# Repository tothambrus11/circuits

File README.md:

# My PCBs
I collect my PCB designs here.

## Categories
- [Audio circuits](audio-circuits/)

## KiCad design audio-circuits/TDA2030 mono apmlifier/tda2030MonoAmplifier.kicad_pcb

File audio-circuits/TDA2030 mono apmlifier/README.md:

# 1x18w mono amplifier

## PCB layout:

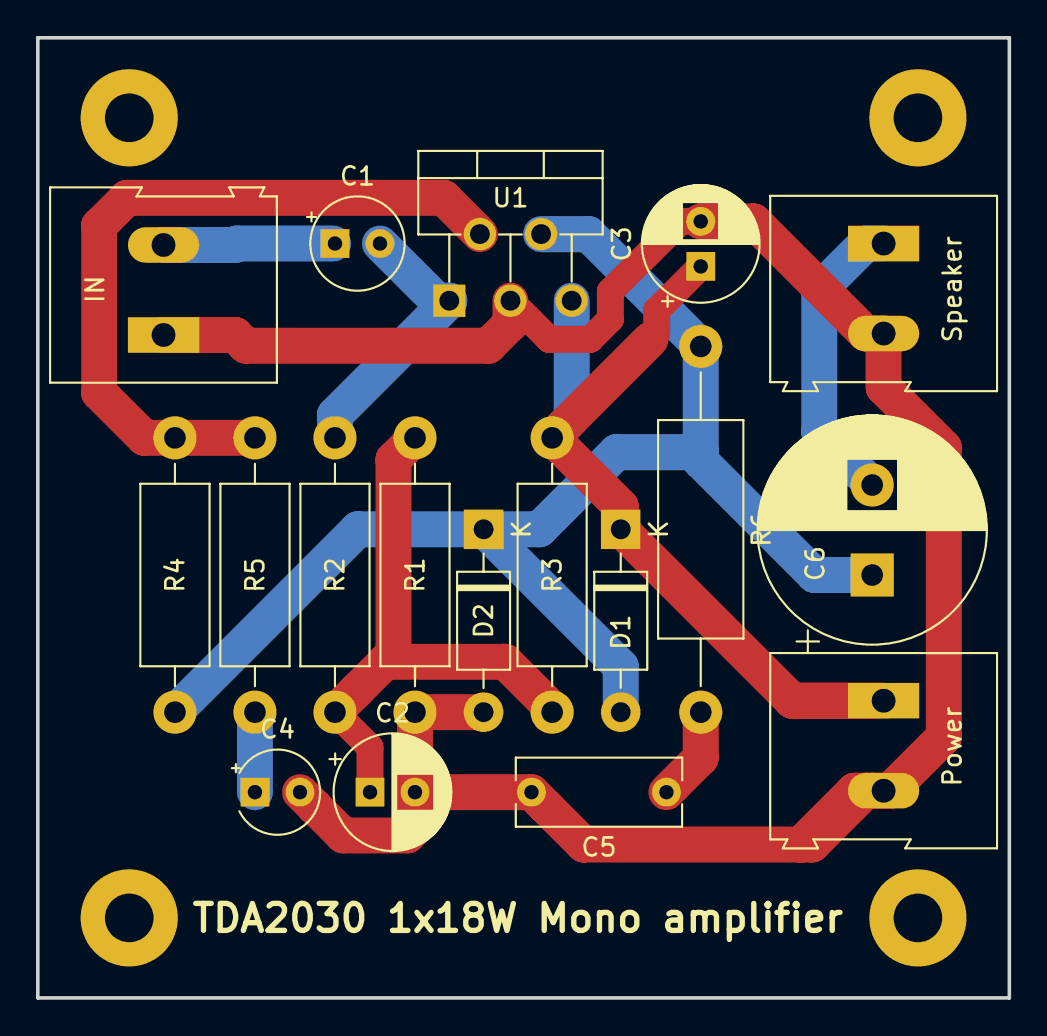
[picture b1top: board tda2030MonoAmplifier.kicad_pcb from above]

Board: 2 copper layers, 54.0 x 53.3 mm, 22 parts (0 on the bottom side), 10 nets.

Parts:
C1: 10u; CP_Radial_Tantal_D5.0mm_P2.50mm
C2, C3: 22u/40V; CP_Radial_D6.3mm_P2.50mm
C4: 4,7u/40V; CP_Radial_Tantal_D4.5mm_P2.50mm
C5: 150n; C_Rect_L9.0mm_W3.6mm_P7.50mm_MKT
C6: 1000u; CP_Radial_D12.5mm_P5.00mm
D1, D2: 1N4007; D_DO-41_SOD81_P10.16mm_Horizontal
IN: IN; TerminalBlock_Altech_AK300-2_P5.00mm
MH1, MH2, MH3, MH4: MountingHole_Pad; MountingHole_2.7mm_M2.5_Pad
Power: Power; TerminalBlock_Altech_AK300-2_P5.00mm
R1, R2, R3: 100k; R_Axial_DIN0411_L9.9mm_D3.6mm_P15.24mm_Horizontal
R4: 150k; R_Axial_DIN0411_L9.9mm_D3.6mm_P15.24mm_Horizontal
R5: 5,6k; R_Axial_DIN0411_L9.9mm_D3.6mm_P15.24mm_Horizontal
R6: 1; R_Axial_DIN0414_L11.9mm_D4.5mm_P20.32mm_Horizontal
Speaker: Speaker L; TerminalBlock_Altech_AK300-2_P5.00mm
U1: TDA2030; TO-220-5_P3.4x3.7mm_StaggerOdd_Lead3.8mm_Vertical

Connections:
GND: C2.2, C3.2, C4.2, C5.2, D2.2, IN.1, Power.2, R1.2, Speaker.2, U1.3
unnamed: C1.1, IN.2
unnamed: C1.2, R2.2, U1.1
unnamed: C2.1, R1.1, R2.1, R3.2
unnamed: C4.1, R5.2
unnamed: C5.1, R6.2
unnamed: C6.1, D1.2, D2.1, R4.1, R6.1, U1.4
unnamed: C6.2, Speaker.1
unnamed: R4.2, R5.1, U1.2
VCC: C3.1, D1.1, Power.1, R3.1, U1.5

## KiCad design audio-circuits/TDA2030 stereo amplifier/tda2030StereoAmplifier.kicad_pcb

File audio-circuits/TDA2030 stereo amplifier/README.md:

# 2x18w stereo amplifier

## PCB layout:

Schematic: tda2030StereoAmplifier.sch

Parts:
C1, C2: 10u; CP_Radial_Tantal_D5.0mm_P2.50mm
C3, C4, C5, C6: 22u/40V; CP_Radial_D6.3mm_P2.50mm
C7, C8: 4,7u/40V; CP_Radial_Tantal_D4.5mm_P2.50mm
C9, C10: 150n; C_Rect_L9.0mm_W3.6mm_P7.50mm_MKT
C11, C12: 1000u; CP_Radial_D12.5mm_P5.00mm
D1, D2, D3, D4: 1N4007; D_DO-41_SOD81_P10.16mm_Horizontal
J1: AUDIO IN; TerminalBlock_Altech_AK300-3_P5.00mm
J2: Power; TerminalBlock_Altech_AK300-2_P5.00mm
LS1: Speaker L; TerminalBlock_Altech_AK300-2_P5.00mm
LS2: Speaker R; TerminalBlock_Altech_AK300-2_P5.00mm
MH1, MH2, MH3, MH4: MountingHole_Pad; MountingHole_2.7mm_M2.5_Pad
R1, R2, R3, R4, R5, R6: 100k; R_Axial_DIN0411_L9.9mm_D3.6mm_P15.24mm_Horizontal
R7, R10: 150k; R_Axial_DIN0411_L9.9mm_D3.6mm_P15.24mm_Horizontal
R8, R9: 5,6k; R_Axial_DIN0411_L9.9mm_D3.6mm_P15.24mm_Horizontal
R11, R12: 1; R_Axial_DIN0414_L11.9mm_D4.5mm_P20.32mm_Horizontal
U1, U2: TDA2030; TO-220-5_P3.4x3.7mm_StaggerOdd_Lead3.8mm_Vertical

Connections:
GND: C3.2, C4.2, C5.2, C6.2, C7.2, C8.2, C9.2, C10.2, D2.2 (A), D3.2 (A), LS1.2, LS2.2, R1.2, R2.2, U1.3, U2.3; also elsewhere on the board
unnamed 1: C1.1; also elsewhere on the board
unnamed: C1.2, R3.2, U1.1
unnamed 3: C2.1; also elsewhere on the board
unnamed: C2.2, R4.2, U2.1
unnamed: C3.1, R1.1, R3.1, R5.2
unnamed: C4.1, R2.1, R4.1, R6.2
unnamed: C7.1, R8.2
unnamed: C8.1, R9.2
unnamed: C9.1, R11.2
unnamed: C10.1, R12.2
unnamed: C11.1, D1.2 (A), D2.1 (K), R7.1, R11.1, U1.4
unnamed: C11.2, LS1.1
unnamed: C12.1, D3.1 (K), D4.2 (A), R10.1, R12.1, U2.4
unnamed: C12.2, LS2.1
unnamed: R7.2, R8.1, U1.2
unnamed: R9.1, R10.2, U2.2
VCC: C5.1, C6.1, D1.1 (K), D4.1 (K), R5.1, R6.1, U1.5, U2.5; also elsewhere on the board

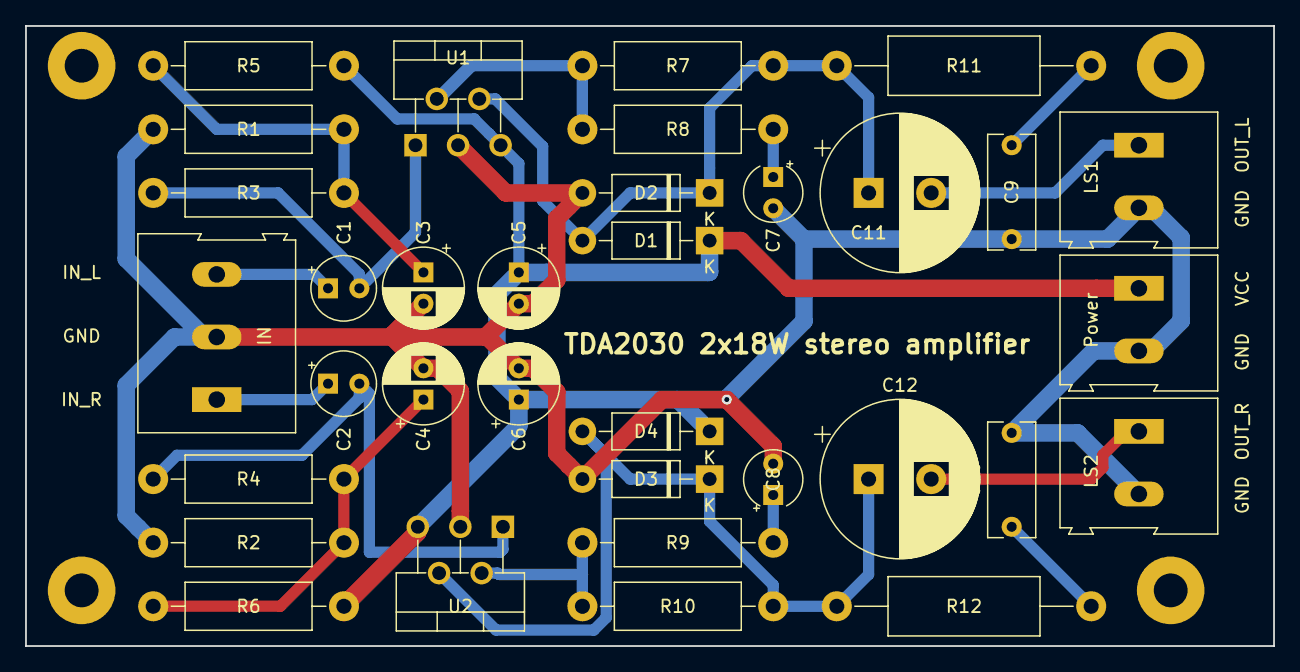
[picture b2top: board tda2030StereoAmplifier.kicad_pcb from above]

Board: 2 copper layers, 99.7 x 49.5 mm, 38 parts (0 on the bottom side), 18 nets.

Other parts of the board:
IN: AUDIO IN; TerminalBlock_Altech_AK300-3_P5.00mm
Power: Power; TerminalBlock_Altech_AK300-2_P5.00mm

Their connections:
GND: IN.2, Power.2; also elsewhere on the board
unnamed 1: IN.3; also elsewhere on the board
unnamed 3: IN.1; also elsewhere on the board
VCC: Power.1; also elsewhere on the board

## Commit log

2018-07-24 TDA2030 stereo amplifier added
2018-07-24 link
2018-07-24 images
2018-07-24 Set theme jekyll-theme-midnight
2018-07-25 TDA2030 mono amplifier added
2018-07-25 link added
2018-07-25 Set theme jekyll-theme-hacker
